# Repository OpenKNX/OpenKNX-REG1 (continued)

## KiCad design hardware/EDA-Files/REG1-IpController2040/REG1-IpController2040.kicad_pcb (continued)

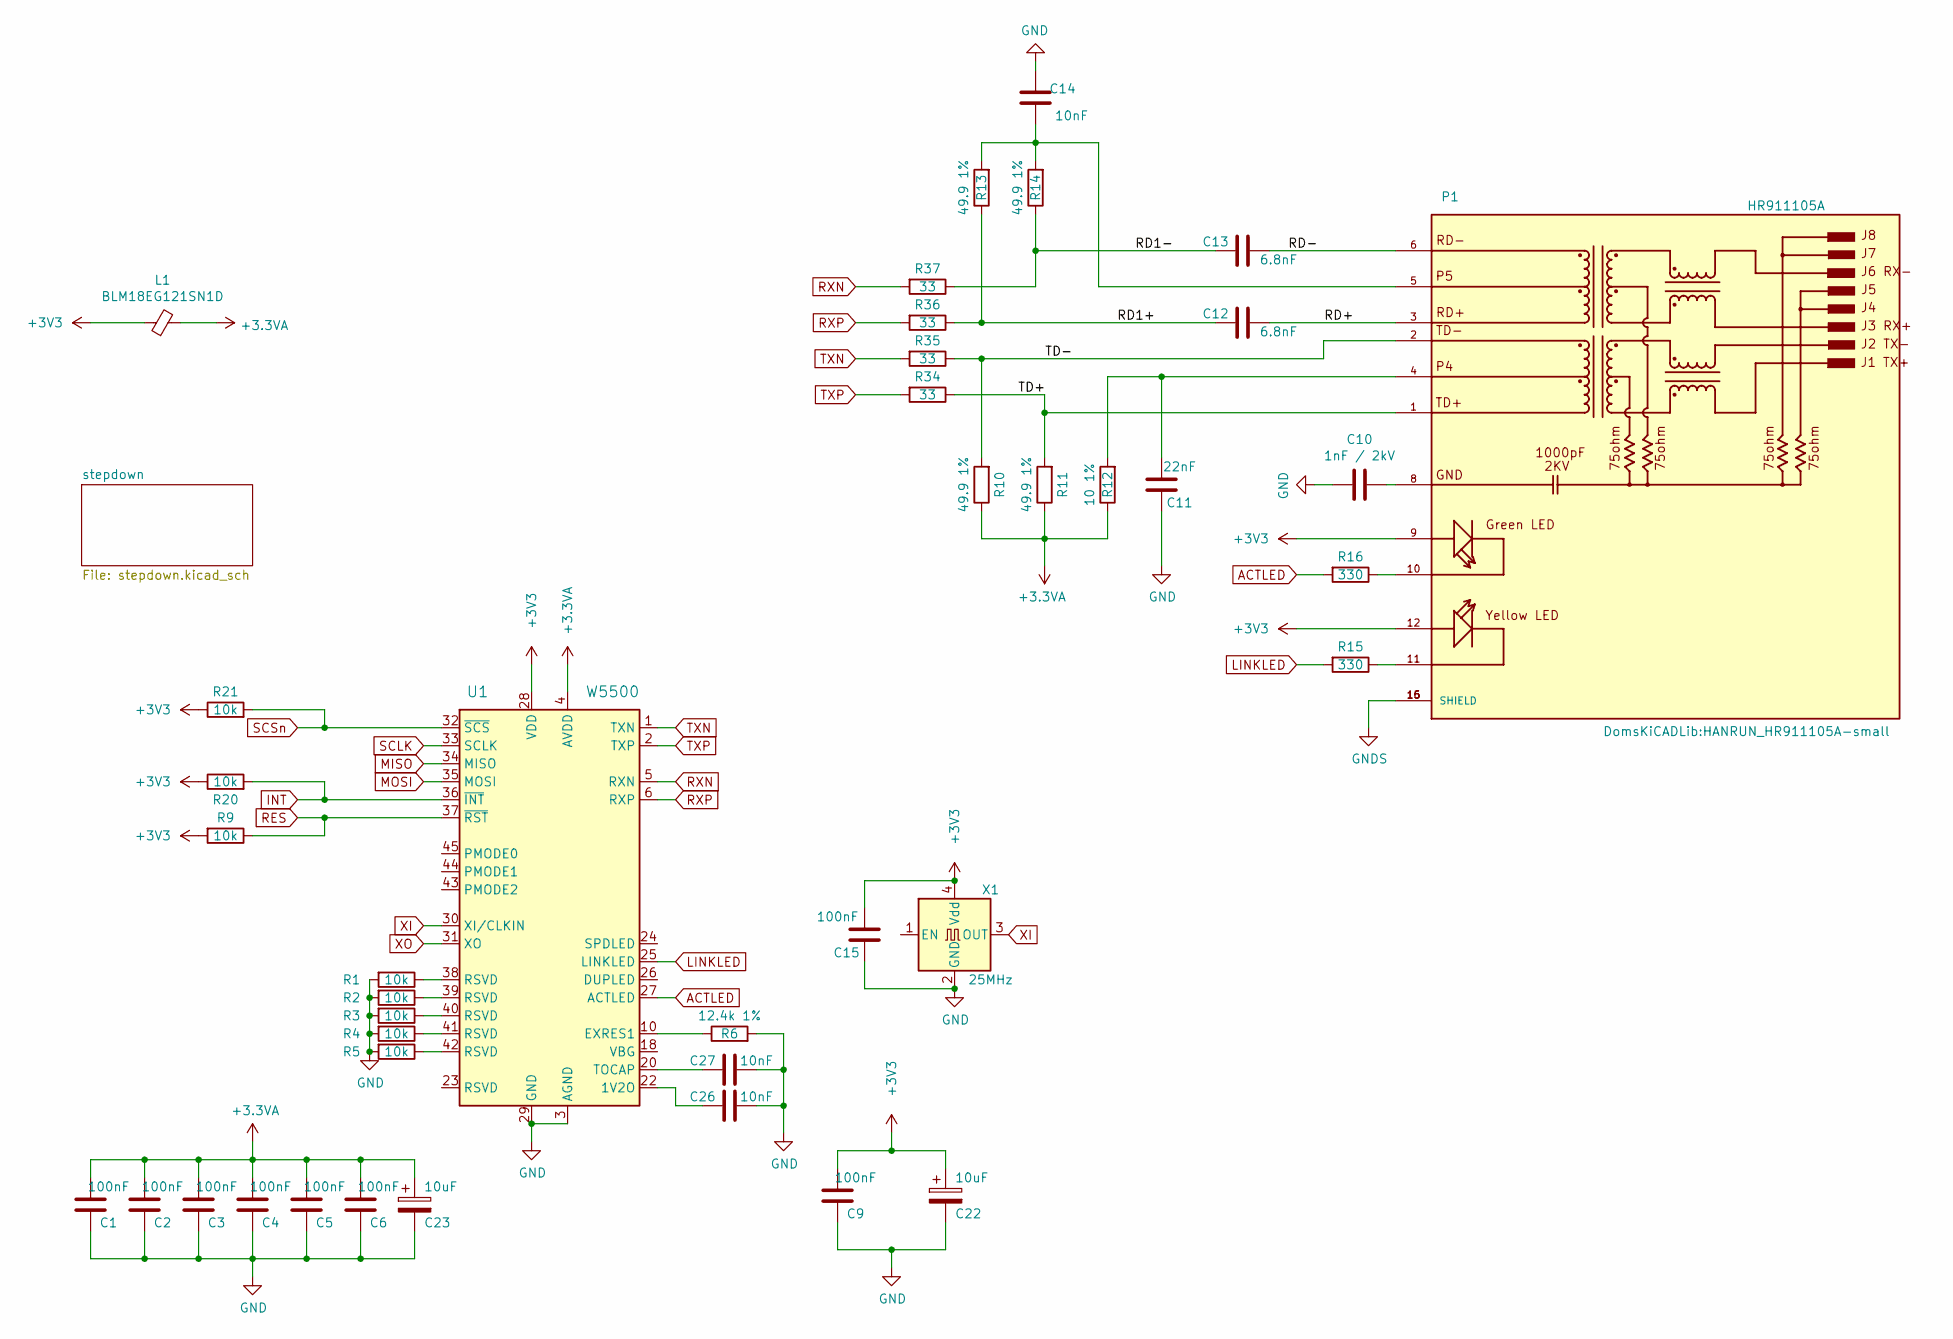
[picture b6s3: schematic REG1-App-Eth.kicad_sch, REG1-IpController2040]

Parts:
C1, C2, C3, C4, C5, C6, C9, C15: 100nF; C_0402_1005Metric
C10: 1nF / 2kV; C_1206_3216Metric
C11: 22nF; C_0402_1005Metric
C12, C13: 6.8nF; C_0402_1005Metric
C14, C26, C27: 10nF; C_0402_1005Metric
C22, C23: 10uF; CP_EIA-3216-18_Kemet-A
L1: BLM18EG121SN1D; L_0603_1608Metric
P1: HR911105A; HANRUN_HR911105A-small; PARTREV A
R1, R2, R3, R4, R5, R9, R20, R21: 10k; R_0402_1005Metric
R6: 12.4k 1%; R_0402_1005Metric
R10, R11, R13, R14: 49.9 1%; R_0402_1005Metric
R12: 10 1%; R_0402_1005Metric
R15, R16: 330; R_0402_1005Metric
R34, R35, R36, R37: 33; R_0402_1005Metric
U1: W5500; LQFP-48_7x7mm_P0.5mm; MPN W5500; Digi-Key_PN 1278-1021-ND
X1: 25MHz; Crystal_SMD_3225-4Pin_3.2x2.5mm

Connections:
+3.3VA: C1.1, C2.1, C3.1, C4.1, C5.1, C6.1, C23.1, L1.2, R10.1, R11.1, R12.1, U1.4 (AVDD), U1.8 (AVDD), U1.11 (AVDD), U1.15 (AVDD), U1.17 (AVDD), U1.21 (AVDD)
+3V3: C9.1, C15.1, C22.1, L1.1, P1.9, P1.12, R9.2, R20.1, R21.1, U1.28 (VDD), X1.4 (Vdd); also elsewhere on the board
/REG1-App-Eth/RD1+: C12.2, R13.1, R36.1
/REG1-App-Eth/RD1-: C13.2, R14.1, R37.1
/REG1-App-Eth/RD+: C12.1, P1.3
/REG1-App-Eth/RD-: C13.1, P1.6
/REG1-App-Eth/TD+: P1.1, R11.2, R34.1
/REG1-App-Eth/TD-: P1.2, R10.2, R35.1
ACTLED: R16.2, U1.27 (ACTLED); also elsewhere on the board
GND: C1.2, C2.2, C3.2, C4.2, C5.2, C6.2, C9.2, C10.2, C11.2, C14.2, C15.2, C22.2, C23.2, C26.1, C27.2, R1.2, R2.2, R3.2, R4.2, R5.2, R6.2, U1.3 (AGND), U1.9 (AGND), U1.14 (AGND), U1.16 (AGND), U1.19 (AGND), U1.29 (GND), U1.48 (AGND), X1.2 (GND); also elsewhere on the board
GNDS: P1.15 (SHIELD), P1.16 (SHIELD)
INT: R20.2, U1.36 (~INT); also elsewhere on the board
LINKLED: R15.2, U1.25 (LINKLED)
MISO: U1.34 (MISO); also elsewhere on the board
MOSI: U1.35 (MOSI); also elsewhere on the board
unnamed: C10.1, P1.8
unnamed: C11.1, P1.4, R12.2
unnamed: C14.1, P1.5, R13.2, R14.2
unnamed: P1.10, R16.1
unnamed: P1.11, R15.1
unnamed: R1.1, U1.38 (RSVD)
unnamed: R2.1, U1.39 (RSVD)
unnamed: R3.1, U1.40 (RSVD)
unnamed: R4.1, U1.41 (RSVD)
unnamed: R5.1, U1.42 (RSVD)
unnamed: C26.2, U1.22 (1V2O)
unnamed: R6.1, U1.10 (EXRES1)
unnamed: C27.1, U1.20 (TOCAP)
RES: R9.1, U1.37 (~RST); also elsewhere on the board
RXN: R37.2, U1.5 (RXN)
RXP: R36.2, U1.6 (RXP)
SCLK: U1.33 (SCLK); also elsewhere on the board
SCSn: R21.2, U1.32 (~SCS); also elsewhere on the board
TXN: R35.2, U1.1 (TXN)
TXP: R34.2, U1.2 (TXP)
XI: U1.30 (XI/CLKIN), X1.3 (OUT)
XO: U1.31 (XO)

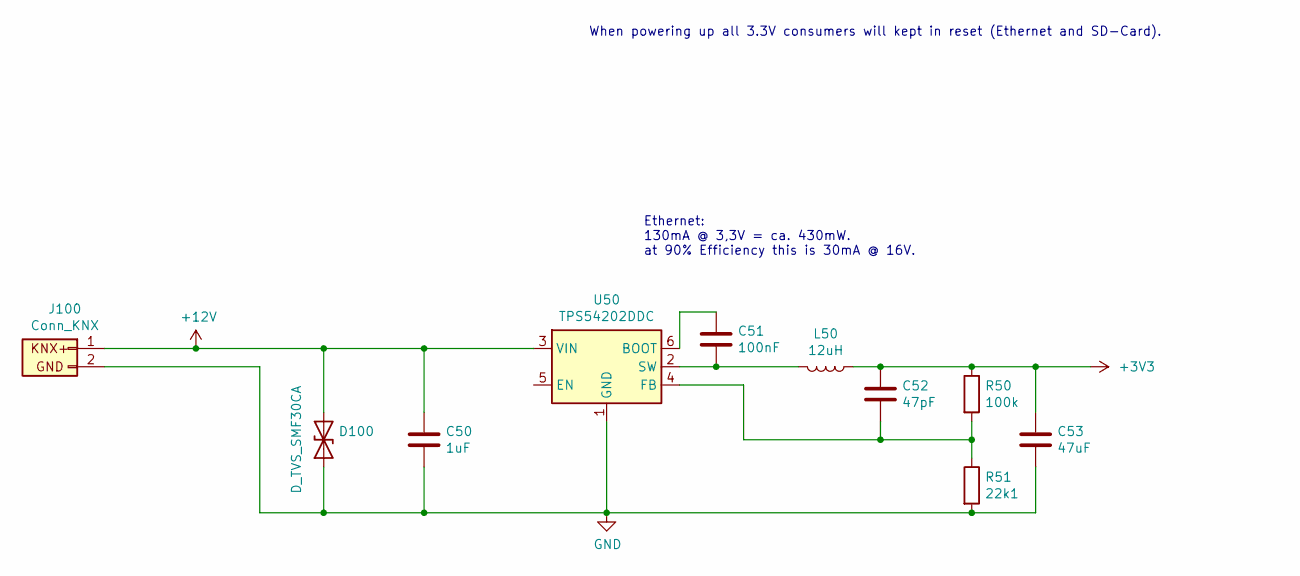
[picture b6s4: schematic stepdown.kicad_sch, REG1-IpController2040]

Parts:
C50: 1uF; C_0805_2012Metric
C51: 100nF; C_0402_1005Metric
C52: 47pF; C_0402_1005Metric
C53: 47uF; C_1206_3216Metric
D100: D_TVS_SMF30CA; D_SOD-123F
J100: Conn_KNX; Wago243_212_Connector
L50: 12uH; L_Sunlord_SWPA4020
R50: 100k; R_0402_1005Metric
R51: 22k1; R_0402_1005Metric
U50: TPS54202DDC; SOT-23-6

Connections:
+3V3: C52.1, C53.1, L50.1, R50.1; also elsewhere on the board
+12V: C50.1, D100.2 (A2), J100.1, U50.3 (VIN); also elsewhere on the board
GND: C50.2, C53.2, D100.1 (A1), J100.2, R51.2, U50.1 (GND); also elsewhere on the board
unnamed: C51.1, U50.6 (BOOT)
unnamed: C52.2, R50.2, R51.1, U50.4 (FB)
unnamed: C51.2, L50.2, U50.2 (SW)

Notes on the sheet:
When powering up all 3.3V consumers will kept in reset (Ethernet and SD-Card).
Ethernet: 130mA @ 3,3V = ca. 430mW. at 90% Efficiency this is 30mA @ 16V.

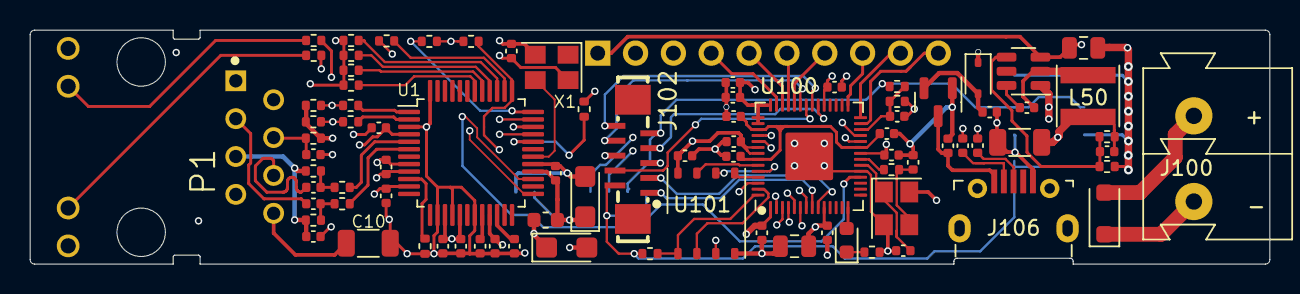
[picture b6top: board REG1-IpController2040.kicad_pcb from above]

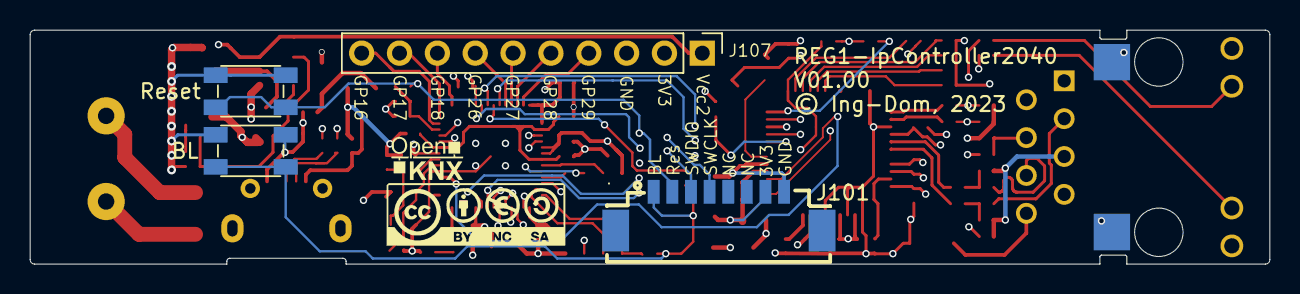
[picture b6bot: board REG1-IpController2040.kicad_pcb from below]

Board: 4 copper layers, 83.2 x 15.7 mm, 89 parts (6 on the bottom side), 76 nets.

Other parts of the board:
G1: LOGO; CC-BY-NY-SA_12x4
G2: LOGO; OpenKNX_Logo_6x6
